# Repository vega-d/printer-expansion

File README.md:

uses rp2040-zero from Waveshare. Only 2 layers, pretty cheap, has uart0 broken out. 3 standard stepstick slots. Uses 2.56mm pinheaders for everything.

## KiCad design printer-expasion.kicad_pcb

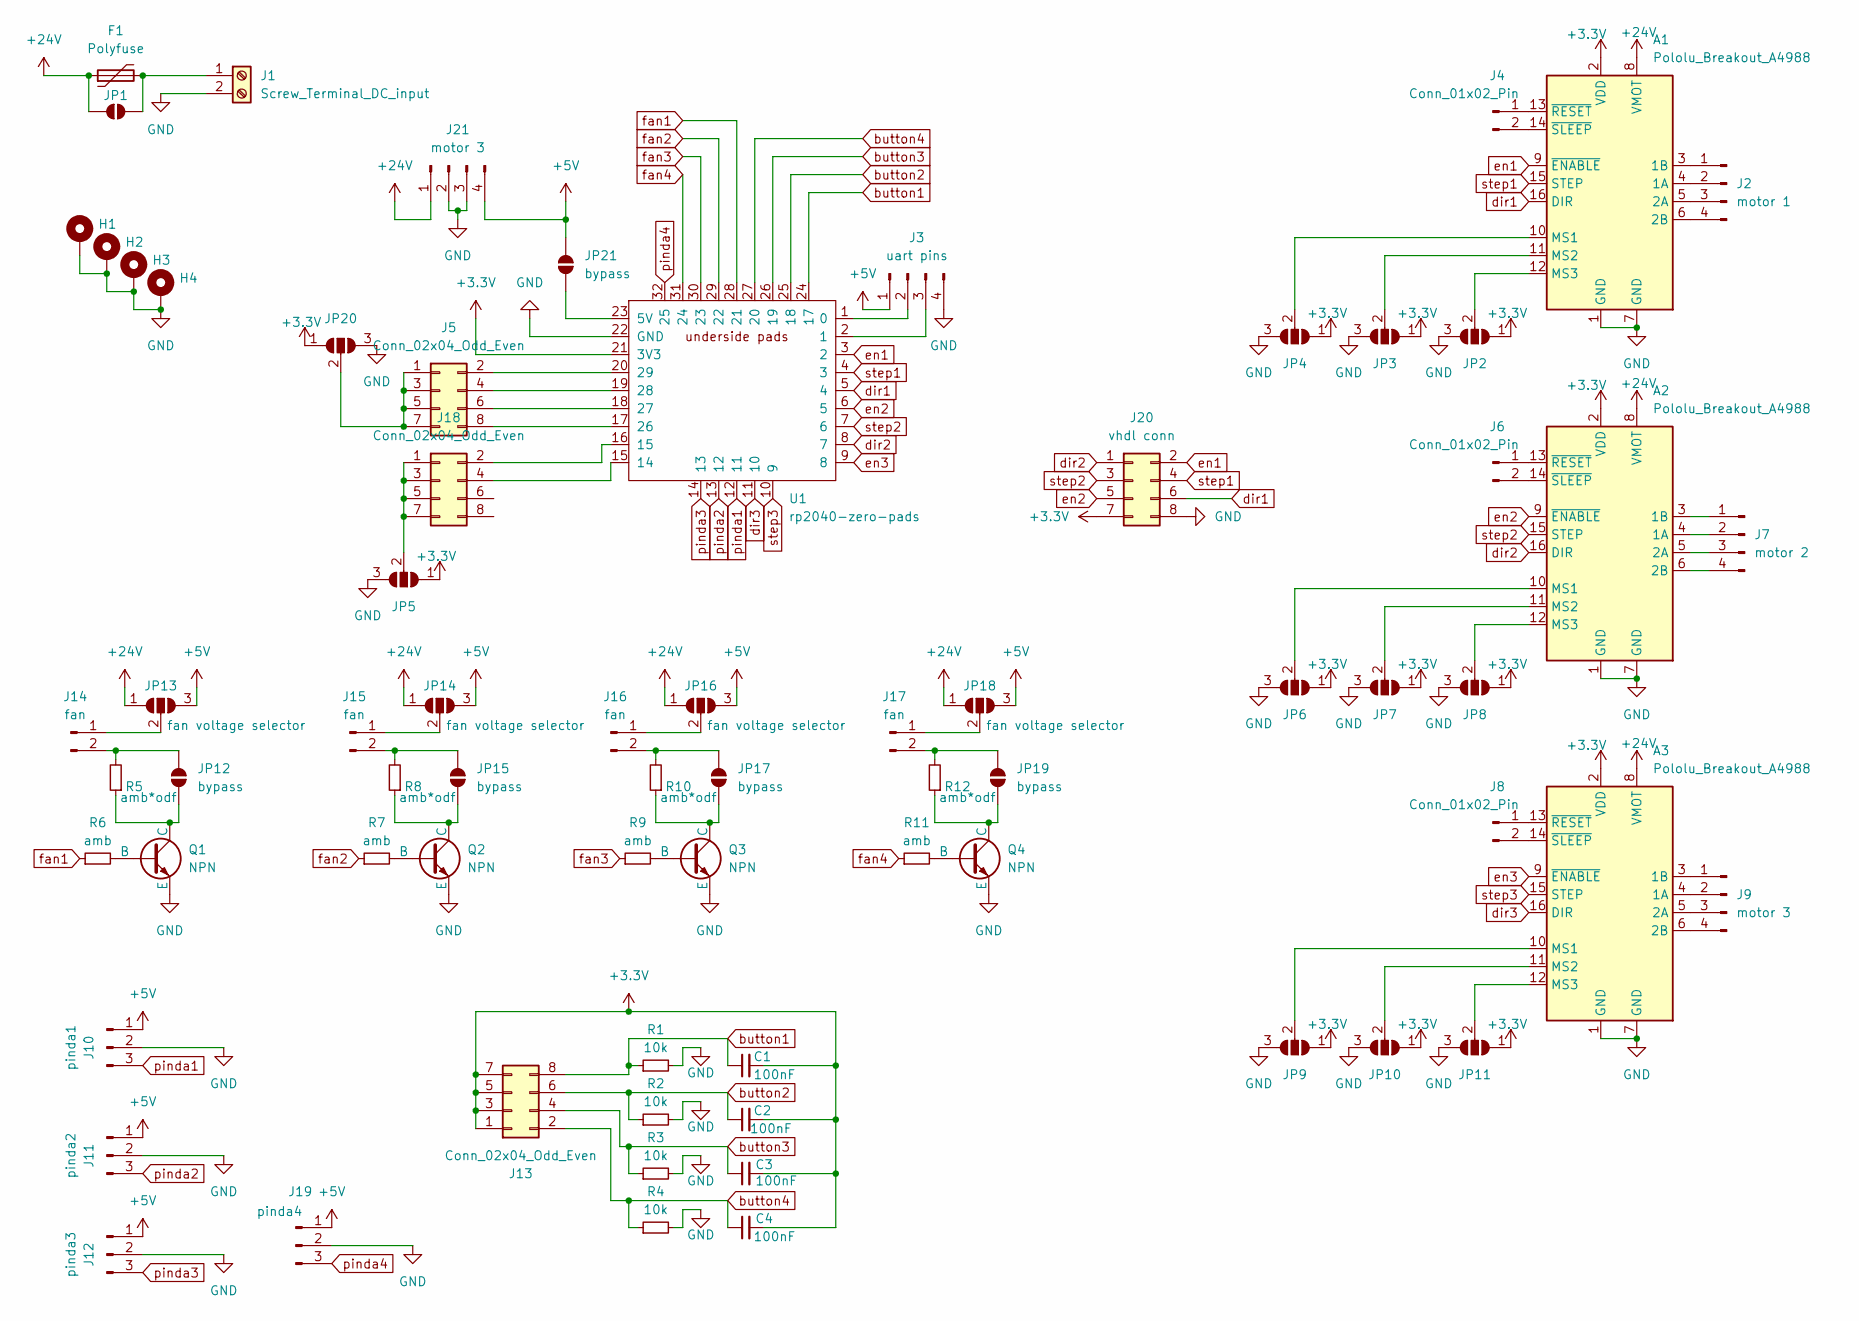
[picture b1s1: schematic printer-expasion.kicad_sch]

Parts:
A1, A2, A3: Pololu_Breakout_A4988; Pololu_Breakout-16_15.2x20.3mm
C1, C2, C3, C4: 100nF; C_Elec_6.3x5.4
F1: Polyfuse; Fuse_Blade_ATO_directSolder
H1, H2, H3, H4: MountingHole_3.2mm_M3_DIN965_Pad
J1: Screw_Terminal_DC_input; TerminalBlock_bornier-2_P5.08mm
J2: motor 1; PinHeader_1x04_P2.54mm_Vertical
J3: uart pins; PinHeader_1x04_P2.54mm_Vertical
J4, J6, J8: Conn_01x02_Pin; PinHeader_1x02_P2.54mm_Vertical
J5, J13, J18: Conn_02x04_Odd_Even; PinHeader_2x04_P2.54mm_Vertical
J7: motor 2; PinHeader_1x04_P2.54mm_Vertical
J9, J21: motor 3; PinHeader_1x04_P2.54mm_Vertical
J10: pinda1; PinHeader_1x03_P2.54mm_Vertical
J11: pinda2; PinHeader_1x03_P2.54mm_Vertical
J12: pinda3; PinHeader_1x03_P2.54mm_Vertical
J14, J15, J16, J17: fan; PinHeader_1x02_P2.54mm_Vertical
J19: pinda4; PinHeader_1x03_P2.54mm_Vertical
J20: vhdl conn; PinHeader_2x04_P2.54mm_Vertical
JP1: SolderJumper_2_Open; SolderJumper-2_P1.3mm_Open_Pad1.0x1.5mm
JP2, JP3, JP4, JP6, JP7, JP8, JP9, JP10, JP11: SolderJumper_3_Open; PinHeader_1x03_P2.54mm_Vertical
JP5, JP20: SolderJumper_3_Open; SolderJumper-3_P1.3mm_Open_Pad1.0x1.5mm
JP12, JP15, JP17, JP19, JP21: bypass; SolderJumper-2_P1.3mm_Open_Pad1.0x1.5mm
JP13, JP14, JP16, JP18: fan voltage selector; SolderJumper-3_P1.3mm_Open_Pad1.0x1.5mm
Q1, Q2, Q3, Q4: NPN; TO-92_Inline_Wide
R1, R2, R3, R4: 10k; R_Axial_DIN0204_L3.6mm_D1.6mm_P5.08mm_Horizontal
R5, R8, R10, R12: amb*odf; R_Axial_DIN0204_L3.6mm_D1.6mm_P5.08mm_Horizontal
R6, R7, R9, R11: amb; R_Axial_DIN0204_L3.6mm_D1.6mm_P5.08mm_Horizontal
U1: rp2040-zero-pads; rp2040-zero-smd-pads-cutout

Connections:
+3.3V: A1.2 (VDD), A2.2 (VDD), A3.2 (VDD), C1.2, C2.2, C3.2, C4.2, J13.1, J13.3, J13.5, J13.7, J20.7, JP2.1 (A), JP3.1 (A), JP4.1 (A), JP5.1 (A), JP6.1 (A), JP7.1 (A), JP8.1 (A), JP9.1 (A), JP10.1 (A), JP11.1 (A), JP20.1 (A), U1.21 (3V3)
+5V: J3.1, J10.1, J11.1, J12.1, J19.1, J21.4, JP13.3 (B), JP14.3 (B), JP16.3 (B), JP18.3 (B), JP21.2 (B)
+24V: A1.8 (VMOT), A2.8 (VMOT), A3.8 (VMOT), F1.1, J21.1, JP1.1 (A), JP13.1 (A), JP14.1 (A), JP16.1 (A), JP18.1 (A)
GND: A1.1 (GND), A1.7 (GND), A2.1 (GND), A2.7 (GND), A3.1 (GND), A3.7 (GND), H1.1, H2.1, H3.1, H4.1, J1.2, J3.4, J10.2, J11.2, J12.2, J19.2, J20.8, J21.2, J21.3, JP2.3 (B), JP3.3 (B), JP4.3 (B), JP5.3 (B), JP6.3 (B), JP7.3 (B), JP8.3 (B), JP9.3 (B), JP10.3 (B), JP11.3 (B), JP20.3 (B), Q1.3 (E), Q2.3 (E), Q3.3 (E), Q4.3 (E), R1.2, R2.2, R3.2, R4.2, U1.22 (GND), U1.33 (GND)
unnamed: A1.4 (1A), J2.2
unnamed: A1.3 (1B), J2.1
unnamed: A1.5 (2A), J2.3
unnamed: A1.6 (2B), J2.4
unnamed: A1.10 (MS1), JP4.2 (C)
unnamed: A1.11 (MS2), JP3.2 (C)
unnamed: A1.12 (MS3), JP2.2 (C)
unnamed: A1.13 (~RESET), J4.1
unnamed: A1.14 (~SLEEP), J4.2
unnamed: A2.4 (1A), J7.2
unnamed: A2.3 (1B), J7.1
unnamed: A2.5 (2A), J7.3
unnamed: A2.6 (2B), J7.4
unnamed: A2.10 (MS1), JP6.2 (C)
unnamed: A2.11 (MS2), JP7.2 (C)
unnamed: A2.12 (MS3), JP8.2 (C)
unnamed: A2.13 (~RESET), J6.1
unnamed: A2.14 (~SLEEP), J6.2
unnamed: A3.4 (1A), J9.2
unnamed: A3.3 (1B), J9.1
unnamed: A3.5 (2A), J9.3
unnamed: A3.6 (2B), J9.4
unnamed: A3.10 (MS1), JP9.2 (C)
unnamed: A3.11 (MS2), JP10.2 (C)
unnamed: A3.12 (MS3), JP11.2 (C)
unnamed: A3.13 (~RESET), J8.1
unnamed: A3.14 (~SLEEP), J8.2
unnamed: F1.2, J1.1, JP1.2 (B)
unnamed: J3.2, U1.1 (0)
unnamed: J3.3, U1.2 (1)
unnamed: J5.1, J5.3, J5.5, J5.7, JP20.2 (C)
unnamed: J5.2, U1.20 (29)
unnamed: J5.4, U1.19 (28)
unnamed: J5.6, U1.18 (27)
unnamed: J5.8, U1.17 (26)
unnamed: J14.1, JP13.2 (C)
unnamed: J14.2, JP12.2 (B), R5.2
unnamed: J15.1, JP14.2 (C)
unnamed: J15.2, JP15.2 (B), R8.2
unnamed: J16.1, JP16.2 (C)
unnamed: J16.2, JP17.2 (B), R10.2
unnamed: J17.1, JP18.2 (C)
unnamed: J17.2, JP19.2 (B), R12.2
unnamed: J18.1, J18.3, J18.5, J18.7, JP5.2 (C)
unnamed: J18.2, U1.16 (15)
unnamed: J18.4, U1.15 (14)
unnamed: JP12.1 (A), Q1.1 (C), R5.1
unnamed: JP15.1 (A), Q2.1 (C), R8.1
unnamed: JP17.1 (A), Q3.1 (C), R10.1
unnamed: JP19.1 (A), Q4.1 (C), R12.1
unnamed: JP21.1 (A), U1.23 (5V)
unnamed: Q1.2 (B), R6.2
unnamed: Q2.2 (B), R7.2
unnamed: Q3.2 (B), R9.2
unnamed: Q4.2 (B), R11.2
button1: C1.1, J13.8, R1.1, U1.24 (17)
button2: C2.1, J13.6, R2.1, U1.25 (18)
button3: C3.1, J13.4, R3.1, U1.26 (19)
button4: C4.1, J13.2, R4.1, U1.27 (20)
dir1: A1.16 (DIR), J20.6, U1.5 (4)
dir2: A2.16 (DIR), J20.1, U1.8 (7)
dir3: A3.16 (DIR), U1.11 (10)
en1: A1.9 (~ENABLE), J20.2, U1.3 (2)
en2: A2.9 (~ENABLE), J20.5, U1.6 (5)
en3: A3.9 (~ENABLE), U1.9 (8)
fan1: R6.1, U1.28 (21)
fan2: R7.1, U1.29 (22)
fan3: R9.1, U1.30 (23)
fan4: R11.1, U1.31 (24)
pinda1: J10.3, U1.12 (11)
pinda2: J11.3, U1.13 (12)
pinda3: J12.3, U1.14 (13)
pinda4: J19.3, U1.32 (25)
step1: A1.15 (STEP), J20.4, U1.4 (3)
step2: A2.15 (STEP), J20.3, U1.7 (6)
step3: A3.15 (STEP), U1.10 (9)

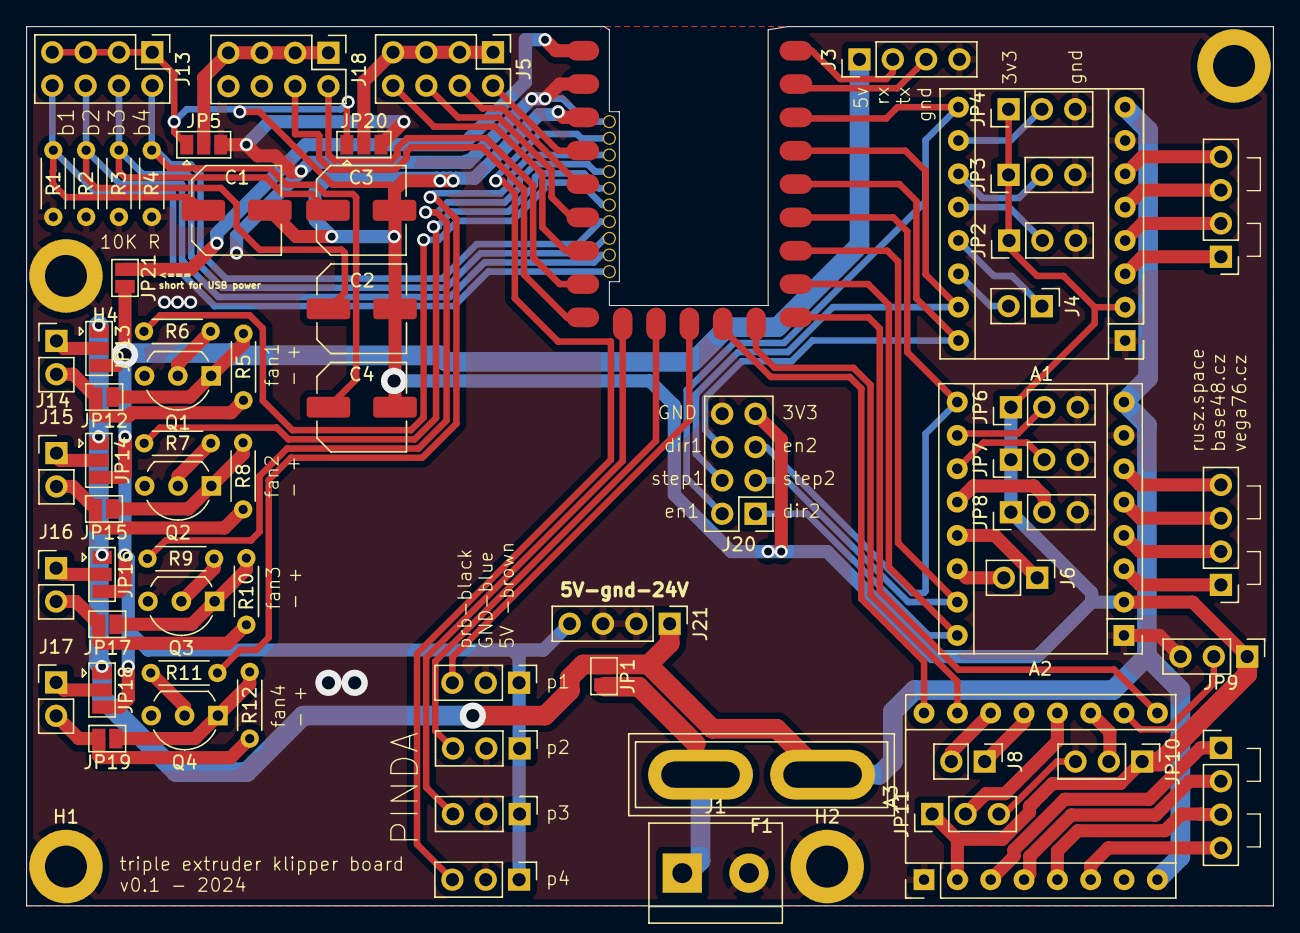
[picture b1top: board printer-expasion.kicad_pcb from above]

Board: 2 copper layers, 95.0 x 67.0 mm, 71 parts (0 on the bottom side), 80 nets.

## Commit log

2024-04-08 init
2024-04-08 get shrunk
2024-06-01 final
